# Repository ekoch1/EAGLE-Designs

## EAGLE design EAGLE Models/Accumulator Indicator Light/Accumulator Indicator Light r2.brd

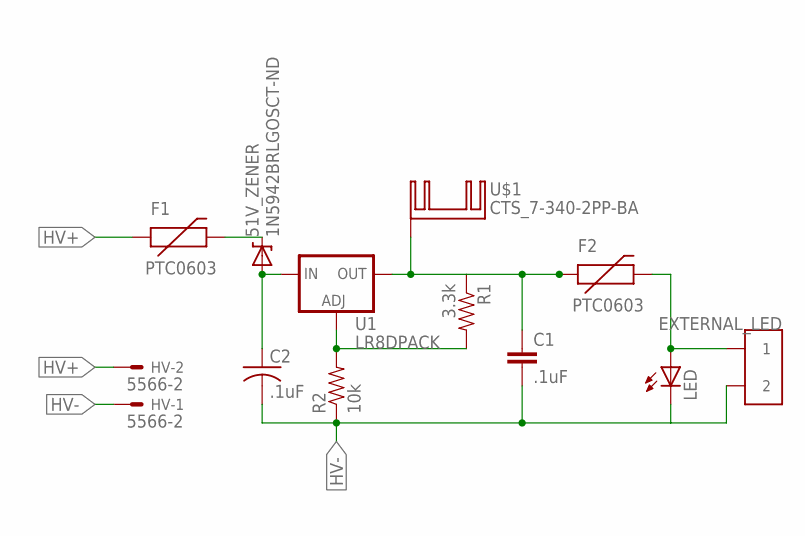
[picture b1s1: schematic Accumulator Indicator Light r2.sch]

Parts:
51V_ZENER: 1N5942BRLGOSCT-ND; DIODE-ZENER
C1: .1uF; 0603-CAP
C2: .1uF; C2220
EXTERNAL_LED: CONN_2; CONNECTOR_2
F1, F2: PTC0603; 0603
HV: 5566-2
LED: LEDSMT1206; 1206
R1: 3.3k; 0603-RES
R2: 10k; 0603-RES
U1: LR8DPACK; DPACK
U$1: CTS_7-340-2PP-BA; TO-200_DUAL

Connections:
HV+: F1.1, HV.2
HV-: C1.2, C2.2, EXTERNAL_LED.3 (2), EXTERNAL_LED.4 (2), HV.1, LED.C, R2.1
N$: 51V_ZENER.P$2 (A), C2.1, U1.1 (IN)
unnamed: R1.2, R2.2, U1.3 (ADJ)
unnamed: C1.1, F2.1, R1.1, U1.4 (OUT), U$1.P$1, U$1.P$2, U$1.P$3
unnamed: 51V_ZENER.P$1 (C), F1.2
unnamed: EXTERNAL_LED.1, EXTERNAL_LED.2 (1), F2.2, LED.A

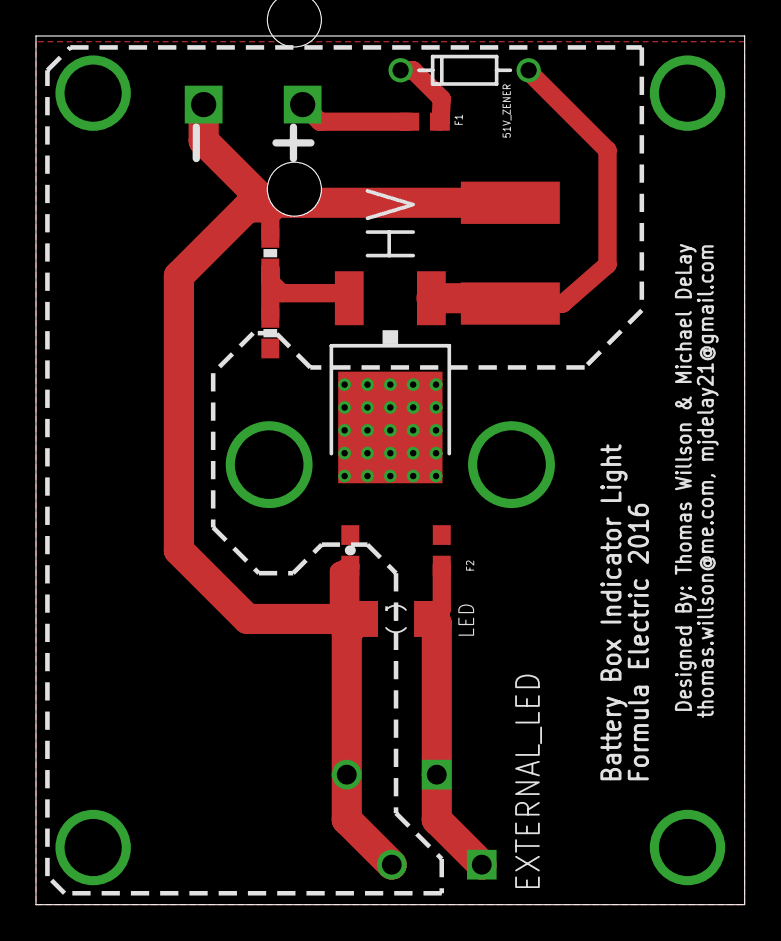
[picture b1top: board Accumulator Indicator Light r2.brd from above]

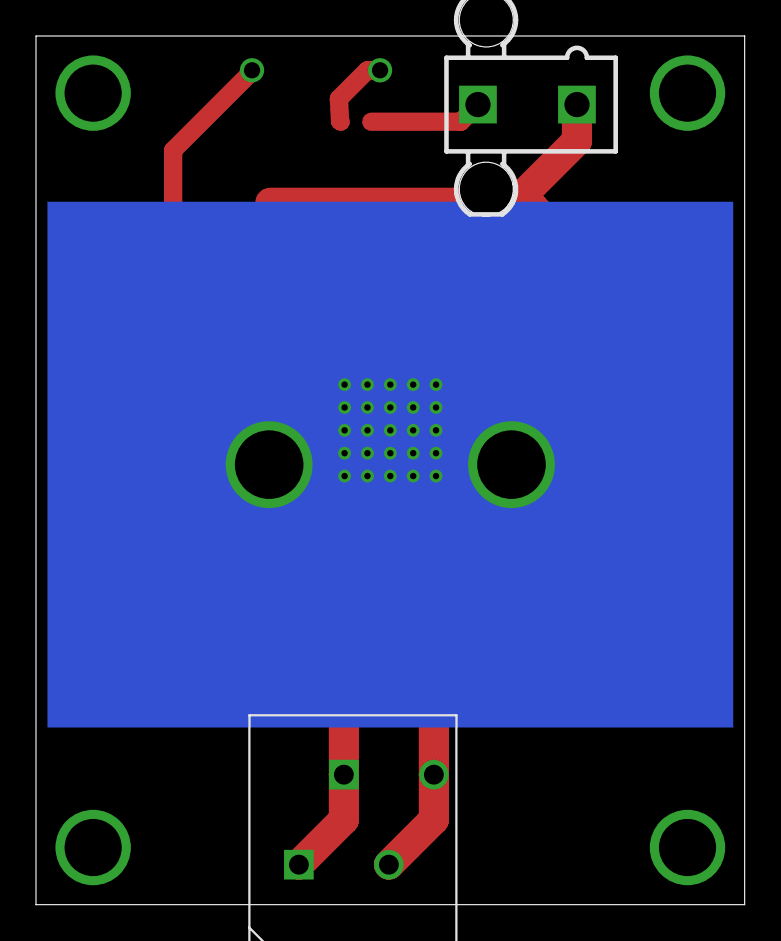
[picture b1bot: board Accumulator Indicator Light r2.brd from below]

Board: 2 copper layers, 39.4 x 48.3 mm, 12 parts (3 on the bottom side), 7 nets.

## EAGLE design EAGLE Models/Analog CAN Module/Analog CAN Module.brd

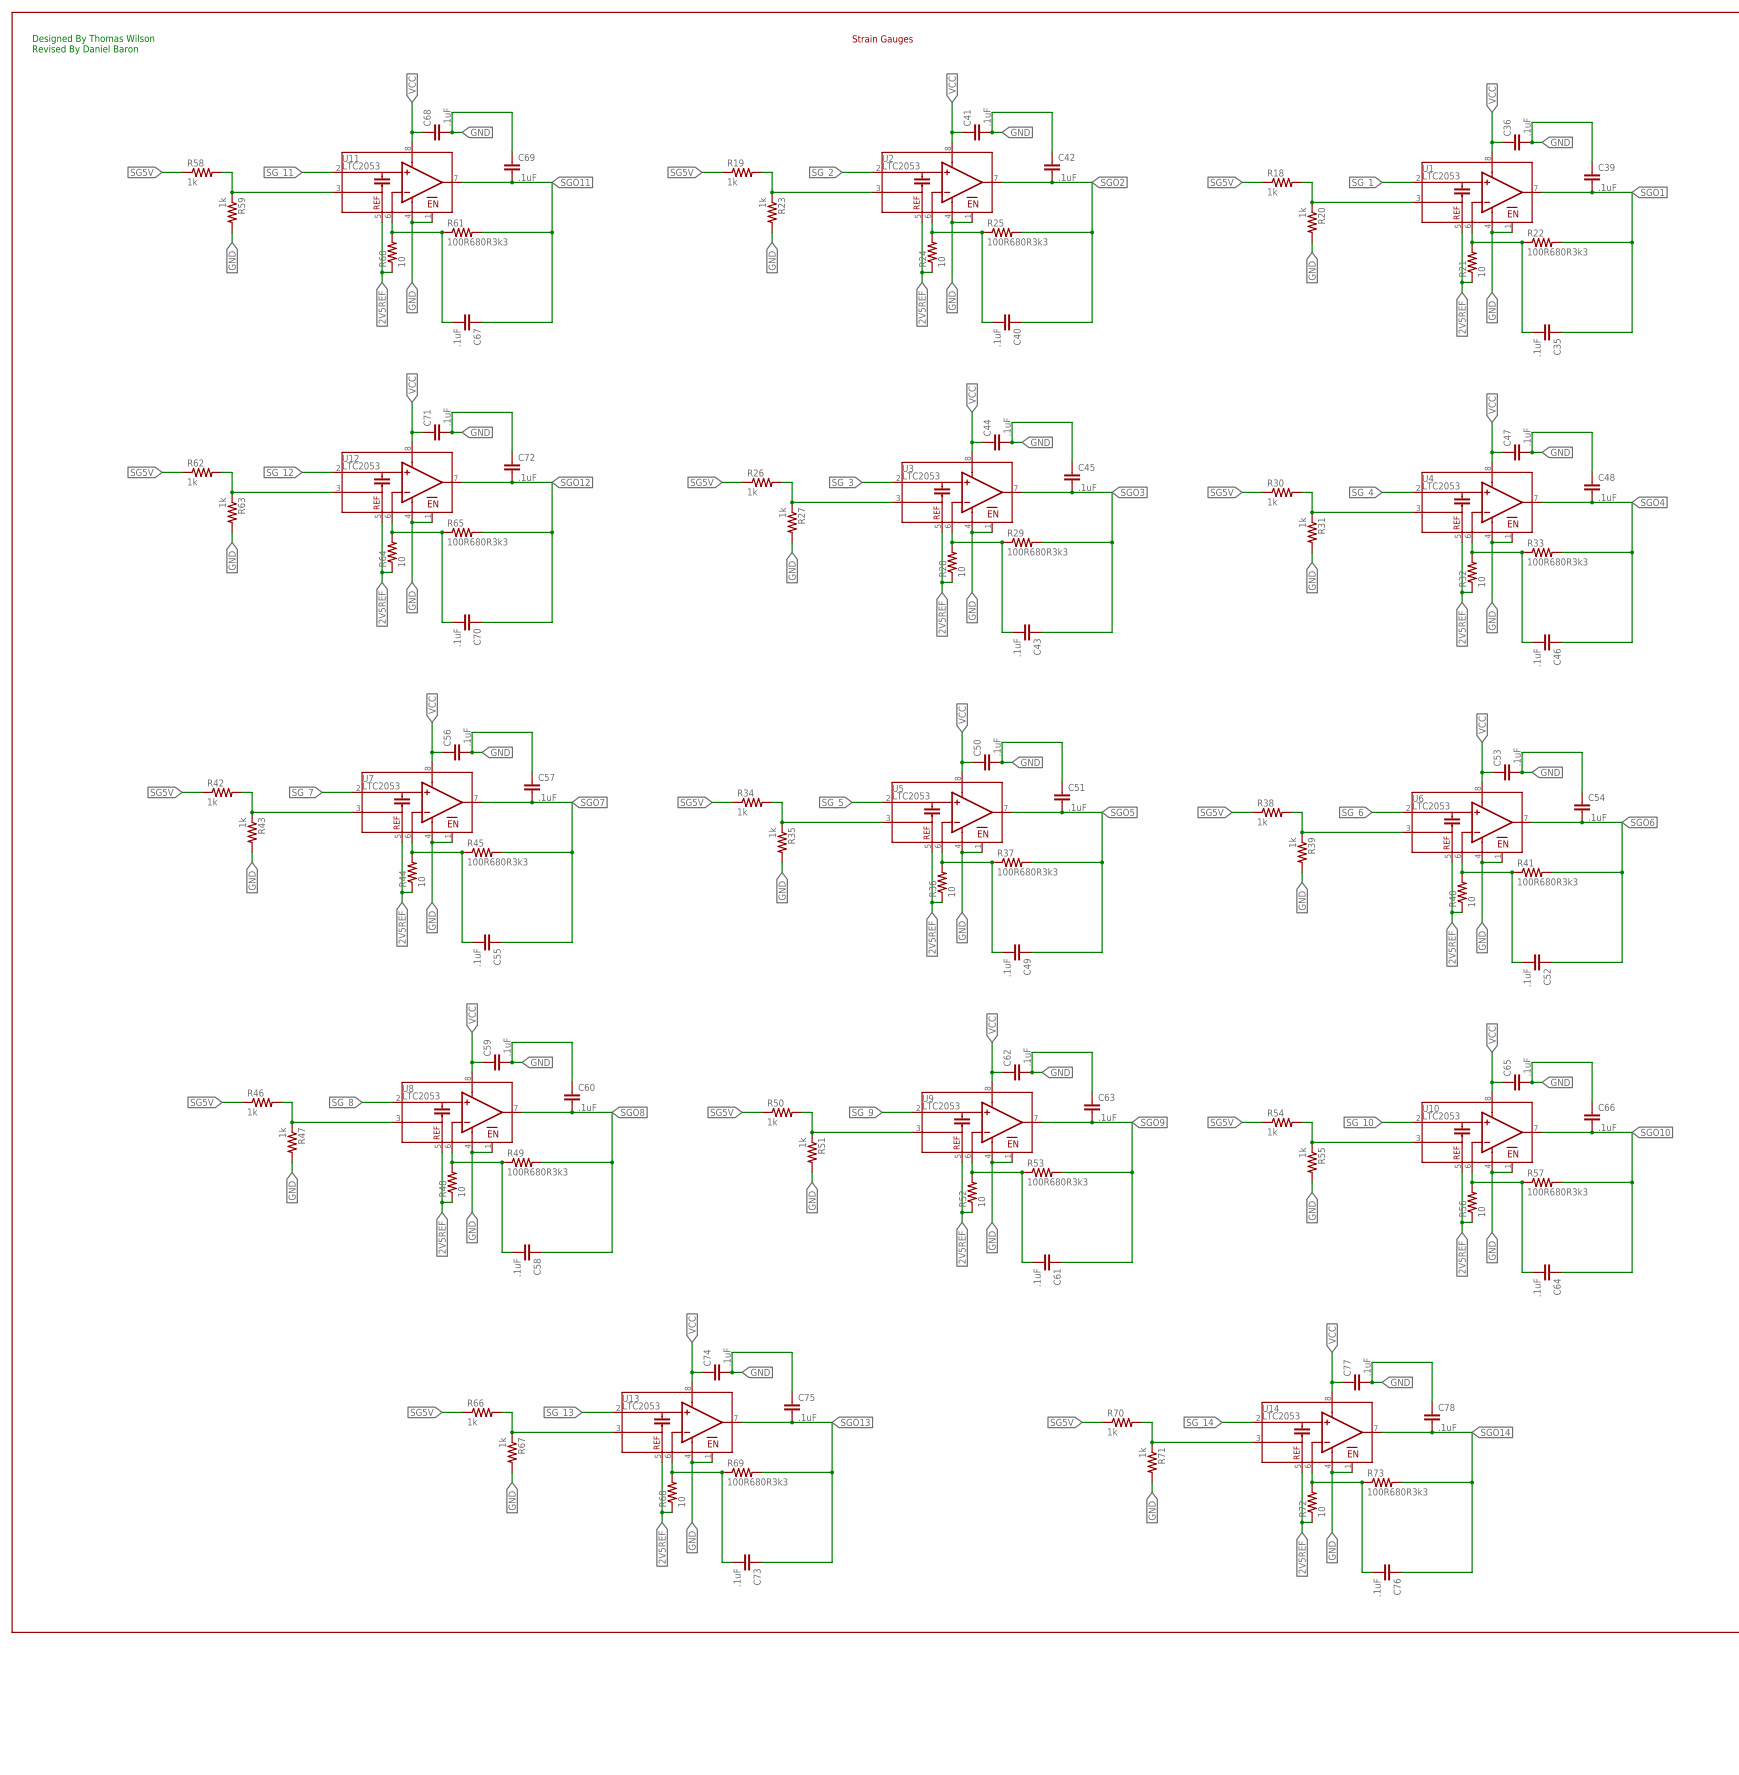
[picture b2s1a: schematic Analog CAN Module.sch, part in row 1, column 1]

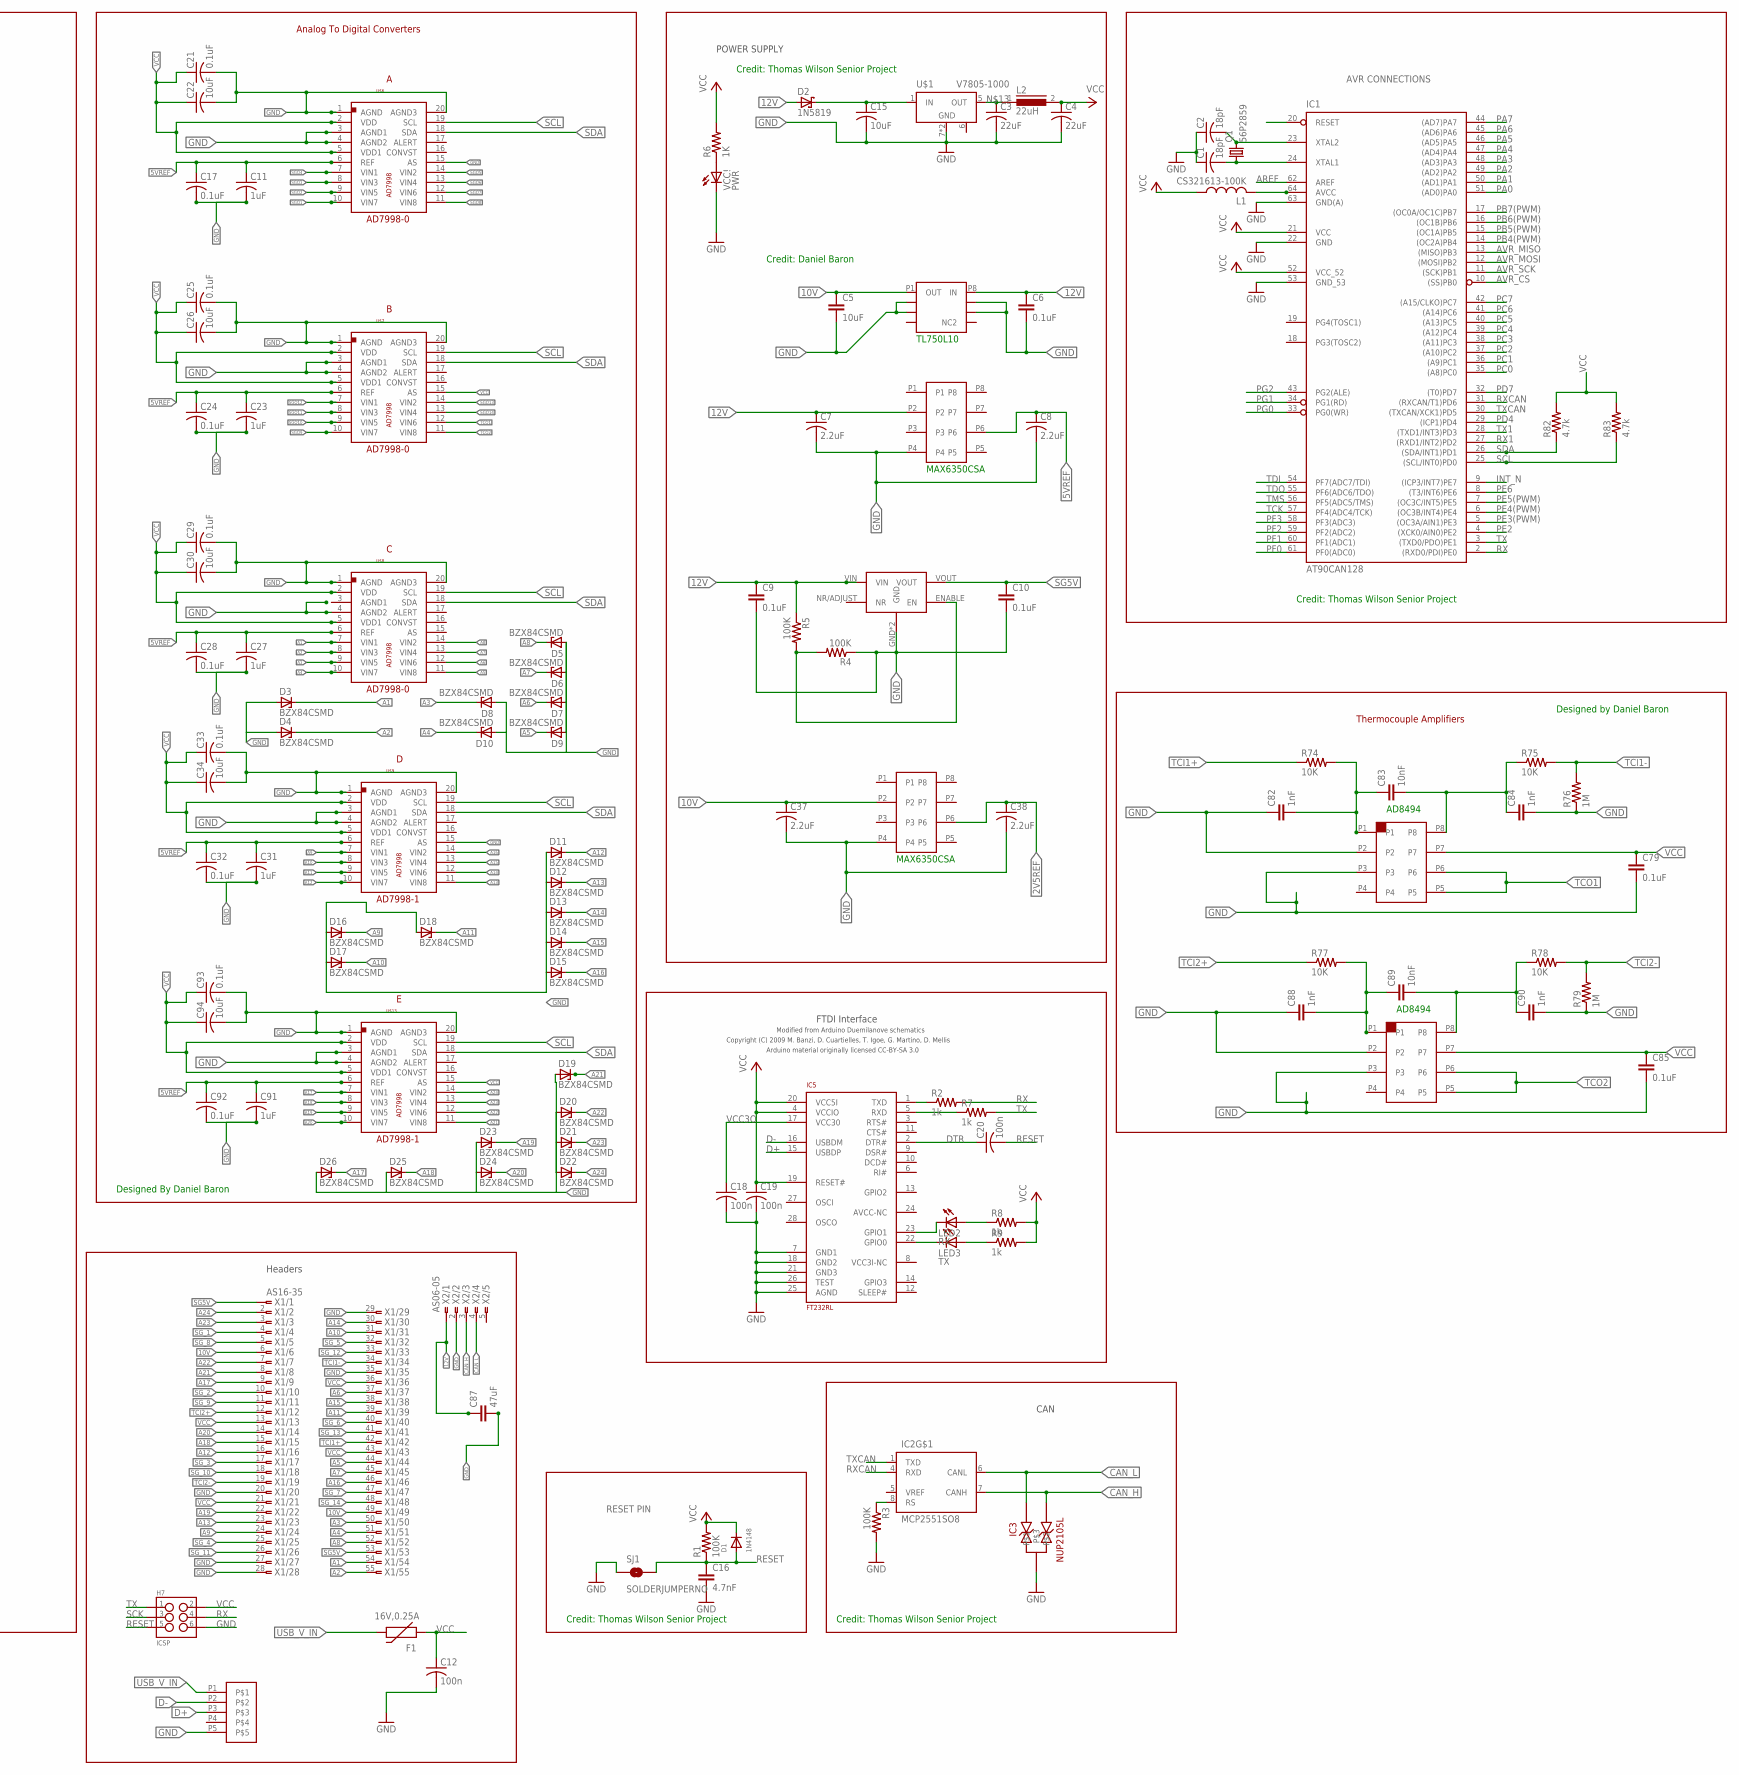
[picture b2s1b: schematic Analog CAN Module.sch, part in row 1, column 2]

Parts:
C1, C2: 18pF; C0805
C3, C4: 22uF; C0805
C5, C15, C22, C26, C30, C34, C94: 10uF; C0805
C6, C9, C10, C17, C21, C24, C25, C28, C29, C32, C33, C79, C85, C92, C93: 0.1uF; C0603
C7, C8, C37, C38: 2.2uF; C0603
C11, C23, C27, C31, C91: 1uF; C0603
C12, C18, C19, C20: 100n; C0805
C16: 4.7nF; 0603-CAP
C35, C36, C39, C40, C41, C42, C43, C44, C45, C46, C47, C48, C49, C50, C51, C52, C53, C54, C55, C56, C57, C58, C59, C60, C61, C62, C63, C64, C65, C66, C67, C68, C69, C70, C71, C72, C73, C74, C75, C76, C77, C78: .1uF; 0603-CAP
C82, C84, C88, C90: 1nF; C0603
C83, C89: 10nF; C0603
C87: 47uF; C0805
D1: 1N4148; SOD-123
D2: 1N5819; DO41-7.6
D3, D4, D5, D6, D7, D8, D9, D10, D11, D12, D13, D14, D15, D16, D17, D18, D19, D20, D21, D22, D23, D24, D25, D26: BZX84CSMD; TO236
F1: 16V,0.25A; PTC-1206
H7: ICSP; 2X3_SMD_FCI_54202-G30
IC1: AT90CAN128; TQFP64
IC2: MCP2551SO8; SO08
IC3: NUP2105L; SOT-23
IC5: FT232RL; SSOP28
L1: CS321613-100K; L3216C
L2: 22uH; DR73
LED2: RX; CHIPLED_0805
LED3: TX; CHIPLED_0805
Q1: 56P2859; HC49UP
R1, R3: 100K; R0805
R2, R7, R8, R9: 1k; R0805
R4, R5: 100K; M0805
R6: 1K; R0805
R18, R19, R20, R23, R26, R27, R30, R31, R34, R35, R38, R39, R42, R43, R46, R47, R50, R51, R54, R55, R58, R59, R62, R63, R66, R67, R70, R71: 1k; 0603-RES
R21, R24, R28, R32, R36, R40, R44, R48, R52, R56, R60, R64, R68, R72: 10; 0603-RES
R22, R25, R29, R33, R37, R41, R45, R49, R53, R57, R61, R65, R69, R73: 100R680R3k3; 0603-RES
R74, R75, R77, R78: 10K; 0603-RES
R76, R79: 1M; 0603-RES
R82, R83: 4.7k; R0805
SJ1: SOLDERJUMPERNO; SJ_2S-NO
U1, U2, U3, U4, U5, U6, U7, U8, U9, U10, U11, U12, U13, U14: LTC2053; MSOP8
U$1: V7805-1000; V78XX-1000
U$2: TL750L10; 8-SOIC
U$4V5V, U$10V2V5: MAX6350CSA; 8-SOIC
U$5: REG-104GA-5; REG104GA-5
U$6, U$7, U$8, U$9, U$13: AD7998; 20TSSOP
U$11, U$12: AD8495; 8MSOP
U$14: MUSBB
VCC!: PWR; CHIPLED_0805
X1: AS16-35
X2: AS06-05

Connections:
2V5REF: C38.1, R21.1, R24.1, R28.1, R32.1, R36.1, R40.1, R44.1, R48.1, R52.1, R56.1, R60.1, R64.1, R68.1, R72.1, U1.5 (REF), U2.5 (REF), U3.5 (REF), U4.5 (REF), U5.5 (REF), U6.5 (REF), U7.5 (REF), U8.5 (REF), U9.5 (REF), U10.5 (REF), U11.5 (REF), U12.5 (REF), U13.5 (REF), U14.5 (REF), U$10V2V5.P6
5VREF: C8.1, C11.1, C17.1, C23.1, C24.1, C27.1, C28.1, C31.1, C32.1, C91.1, C92.1, U$4V5V.P6, U$6.6 (REF), U$7.6 (REF), U$8.6 (REF), U$9.6 (REF), U$13.6 (REF)
10V: C5.1, C37.1, U$2.P1 (OUT), U$10V2V5.P2, X1.6, X1.49
12V: C6.1, C7.1, C9.1, C87.1, D2.A, R5.1, U$2.P8 (IN), U$4V5V.P2, U$5.VIN, X2.1
12V_PROTECTED: C15.1, D2.C, U$1.1 (IN)
A1: D3.C, U$8.7 (VIN1), X1.54
A2: D4.C, U$8.8 (VIN3), X1.55
A3: D8.C, U$8.9 (VIN5), X1.50
A4: D10.C, U$8.10 (VIN7), X1.51
A5: D9.C, U$8.11 (VIN8), X1.44
A6: D7.C, U$8.12 (VIN6), X1.37
A7: D6.C, U$8.13 (VIN4), X1.45
A8: D5.C, U$8.14 (VIN2), X1.52
A9: D16.C, U$9.7 (VIN1), X1.24
A10: D17.C, U$9.8 (VIN3), X1.31
A11: D18.C, U$9.9 (VIN5), X1.39
A12: D11.C, U$9.10 (VIN7), X1.16
A13: D12.C, U$9.11 (VIN8), X1.23
A14: D13.C, U$9.12 (VIN6), X1.30
A15: D14.C, U$9.13 (VIN4), X1.38
A16: D15.C, U$9.14 (VIN2), X1.46
A17: D26.C, U$13.7 (VIN1), X1.9
A18: D25.C, U$13.8 (VIN3), X1.15
A19: D23.C, U$13.9 (VIN5), X1.22
A20: D24.C, U$13.10 (VIN7), X1.14
A21: D19.C, U$13.11 (VIN8), X1.8
A22: D20.C, U$13.12 (VIN6), X1.7
A23: D21.C, U$13.13 (VIN4), X1.3
A24: D22.C, U$13.14 (VIN2), X1.2
AREF: IC1.62 (AREF)
AVR_CS: IC1.10 ((SS)PB0)
AVR_MISO: IC1.13 ((MISO)PB3)
AVR_MOSI: IC1.12 ((MOSI)PB2)
AVR_SCK: IC1.11 ((SCK)PB1)
CAN_H: IC2.7 (CANH), IC3.2, X2.3
CAN_L: IC2.6 (CANL), IC3.1, X2.4
D+: IC5.15 (USBDP), U$14.P3
D-: IC5.16 (USBDM), U$14.P2
DTR: C20.1, IC5.2 (DTR#)
GND: C1.1, C2.1, C3.2, C4.2, C5.2, C6.2, C7.2, C8.2, C9.2, C10.2, C11.2, C12.2, C15.2, C16.2, C17.2, C18.2, C19.2, C21.2, C22.2, C23.2, C24.2, C25.2, C26.2, C27.2, C28.2, C29.2, C30.2, C31.2, C32.2, C33.2, C34.2, C36.2, C37.2, C38.2, C39.1, C41.2, C42.1, C44.2, C45.1, C47.2, C48.1, C50.2, C51.1, C53.2, C54.1, C56.2, C57.1, C59.2, C60.1, C62.2, C63.1, C65.2, C66.1, C68.2, C69.1, C71.2, C72.1, C74.2, C75.1, C77.2, C78.1, C79.2, C82.1, C84.2, C85.2, C87.2, C88.1, C90.2, C91.2, C92.2, C93.2, C94.2, D3.A, D4.A, D5.A, D6.A, D7.A, D8.A, D9.A, D10.A, D11.A, D12.A, D13.A, D14.A, D15.A, D16.A, D17.A, D18.A, D19.A, D20.A, D21.A, D22.A, D23.A, D24.A, D25.A, D26.A, H7.6, IC1.22 (GND), IC1.53 (GND_53), IC1.63 (GND(A)), IC2.2 (GND), IC3.3, IC5.7 (GND1), IC5.18 (GND2), IC5.21 (GND3), IC5.25 (AGND), IC5.26 (TEST), R3.2, R4.1, R20.2, R23.2, R27.2, R31.2, R35.2, R39.2, R43.2, R47.2, R51.2, R55.2, R59.2, R63.2, R67.2, R71.2, R76.1, R79.1, SJ1.1, U1.1 (EN), U1.4 (V-), U2.1 (EN), U2.4 (V-), U3.1 (EN), U3.4 (V-), U4.1 (EN), U4.4 (V-), U5.1 (EN), U5.4 (V-), U6.1 (EN), U6.4 (V-), U7.1 (EN), U7.4 (V-), U8.1 (EN), U8.4 (V-), U9.1 (EN), U9.4 (V-), U10.1 (EN), U10.4 (V-), U11.1 (EN), U11.4 (V-), U12.1 (EN), U12.4 (V-), U13.1 (EN), U13.4 (V-), U14.1 (EN), U14.4 (V-), U$1.7 (GND), U$1.9 (GND), U$2.P2 (COM), U$2.P3 (COM2), U$2.P6 (COM3), U$2.P7 (COM4), U$4V5V.P4, U$5.GND, U$5.HEATGND (GND), U$6.1 (AGND), U$6.3 (AGND1), U$6.4 (AGND2), U$6.15 (AS), U$6.20 (AGND3), U$7.1 (AGND), U$7.3 (AGND1), U$7.4 (AGND2), U$7.20 (AGND3), U$8.1 (AGND), U$8.4 (AGND2), U$8.20 (AGND3), U$9.1 (AGND), U$9.3 (AGND1), U$9.4 (AGND2), U$9.15 (AS), U$9.20 (AGND3), U$10V2V5.P4, U$11.P2, U$11.P3, U$12.P2, U$12.P3, U$13.1 (AGND), U$13.3 (AGND1), U$13.4 (AGND2), U$13.20 (AGND3), U$14.P5, VCC!.C, X1.20, X1.27, X1.28, X1.29, X1.35, X2.2
INT_N: IC1.9 ((ICP3/INT7)PE7)
M8RXD: IC5.1 (TXD), R2.1
M8TXD: IC5.5 (RXD), R7.1
unnamed: C35.2, R21.2, R22.1, U1.6 (RG)
unnamed: R4.2, R5.2, U$5.ENABLE (EN)
unnamed: R66.2, R67.1, U13.3 (+IN)
unnamed: R18.2, R20.1, U1.3 (+IN)
unnamed: R19.2, R23.1, U2.3 (+IN)
unnamed: IC2.8 (RS), R3.1
unnamed: C40.2, R24.2, R25.1, U2.6 (RG)
unnamed: R26.2, R27.1, U3.3 (+IN)
unnamed: R6.1, VCC!.A
unnamed: C43.2, R28.2, R29.1, U3.6 (RG)
unnamed: C1.2, IC1.24 (XTAL1), Q1.1
unnamed: R30.2, R31.1, U4.3 (+IN)
unnamed: C3.1, L2.1, U$1.5 (OUT)
unnamed: C46.2, R32.2, R33.1, U4.6 (RG)
unnamed: R34.2, R35.1, U5.3 (+IN)
unnamed: C49.2, R36.2, R37.1, U5.6 (RG)
unnamed: R38.2, R39.1, U6.3 (+IN)
unnamed: C52.2, R40.2, R41.1, U6.6 (RG)
unnamed: R42.2, R43.1, U7.3 (+IN)
unnamed: C55.2, R44.2, R45.1, U7.6 (RG)
unnamed: R46.2, R47.1, U8.3 (+IN)
unnamed: IC1.64 (AVCC), L1.2
unnamed: C58.2, R48.2, R49.1, U8.6 (RG)
unnamed: R50.2, R51.1, U9.3 (+IN)
unnamed: C61.2, R52.2, R53.1, U9.6 (RG)
unnamed: R54.2, R55.1, U10.3 (+IN)
unnamed: C64.2, R56.2, R57.1, U10.6 (RG)
unnamed: R58.2, R59.1, U11.3 (+IN)
unnamed: C67.2, R60.2, R61.1, U11.6 (RG)
unnamed: R62.2, R63.1, U12.3 (+IN)
unnamed: C70.2, R64.2, R65.1, U12.6 (RG)
unnamed: IC5.23 (GPIO1), LED2.C
unnamed: C73.2, R68.2, R69.1, U13.6 (RG)
unnamed: IC5.22 (GPIO0), LED3.C
unnamed: LED2.A, R8.1
unnamed: LED3.A, R9.1
unnamed: R70.2, R71.1, U14.3 (+IN)
unnamed: C76.2, R72.2, R73.1, U14.6 (RG)
unnamed: C88.2, C89.1, R77.2, U$12.P1
unnamed: C83.2, C84.1, R75.1, U$11.P8
unnamed: C89.2, C90.1, R78.1, U$12.P8
unnamed: C82.2, C83.1, R74.2, U$11.P1
PA0: IC1.51 ((AD0)PA0)
PA1: IC1.50 ((AD1)PA1)
PA2: IC1.49 ((AD2)PA2)
PA3: IC1.48 ((AD3)PA3)
PA4: IC1.47 ((AD4)PA4)
PA5: IC1.46 ((AD5)PA5)
PA6: IC1.45 ((AD6)PA6)
PA7: IC1.44 ((AD7)PA7)
PB4(PWM): IC1.14 ((OC2A)PB4)
PB5(PWM): IC1.15 ((OC1A)PB5)
PB6(PWM): IC1.16 ((OC1B)PB6)
PB7(PWM): IC1.17 ((OC0A/OC1C)PB7)
PC0: IC1.35 ((A8)PC0)
PC1: IC1.36 ((A9)PC1)
PC2: IC1.37 ((A10)PC2)
PC3: IC1.38 ((A11)PC3)
PC4: IC1.39 ((A12)PC4)
PC5: IC1.40 ((A13)PC5)
PC6: IC1.41 ((A14)PC6)
PC7: IC1.42 ((A15/CLKO)PC7)
PD4: IC1.29 ((ICP1)PD4)
PD7: IC1.32 ((T0)PD7)
PE2: IC1.4 ((XCK0/AIN0)PE2)
PE3(PWM): IC1.5 ((OC3A/AIN1)PE3)
PE4(PWM): IC1.6 ((OC3B/INT4)PE4)
PE5(PWM): IC1.7 ((OC3C/INT5)PE5)
PE6: IC1.8 ((T3/INT6)PE6)
PF0: IC1.61 (PF0(ADC0))
PF1: IC1.60 (PF1(ADC1))
PF2: IC1.59 (PF2(ADC2))
PF3: IC1.58 (PF3(ADC3))
PG0: IC1.33 (PG0(WR))
PG1: IC1.34 (PG1(RD))
PG2: IC1.43 (PG2(ALE))
RESET: C16.1, C20.2, D1.A, H7.5, IC1.20 (RESET), R1.1, SJ1.2
RX: H7.4, IC1.2 ((RXD0/PDI)PE0), R2.2
RX1: IC1.27 ((RXD1/INT2)PD2)
RXCAN: IC1.31 ((RXCAN/T1)PD6), IC2.4 (RXD)
SCK: H7.3
SCL: IC1.25 ((SCL/INT0)PD0), R83.1, U$6.19 (SCL), U$7.19 (SCL), U$8.19 (SCL), U$9.19 (SCL), U$13.19 (SCL)
SDA: IC1.26 ((SDA/INT1)PD1), R82.1, U$6.18 (SDA), U$7.18 (SDA), U$8.18 (SDA), U$9.18 (SDA), U$13.18 (SDA)
SG5V: C10.1, R18.1, R19.1, R26.1, R30.1, R34.1, R38.1, R42.1, R46.1, R50.1, R54.1, R58.1, R62.1, R66.1, R70.1, U$5.VOUT, X1.1, X1.53
SGO1: C35.1, C39.2, R22.2, U1.7 (OUT), U$6.10 (VIN7)
SGO2: C40.1, C42.2, R25.2, U2.7 (OUT), U$6.9 (VIN5)
SGO3: C43.1, C45.2, R29.2, U3.7 (OUT), U$6.8 (VIN3)
SGO4: C46.1, C48.2, R33.2, U4.7 (OUT), U$6.7 (VIN1)
SGO5: C49.1, C51.2, R37.2, U5.7 (OUT), U$6.14 (VIN2)
SGO6: C52.1, C54.2, R41.2, U6.7 (OUT), U$6.13 (VIN4)
SGO7: C55.1, C57.2, R45.2, U7.7 (OUT), U$6.12 (VIN6)
SGO8: C58.1, C60.2, R49.2, U8.7 (OUT), U$6.11 (VIN8)
SGO9: C61.1, C63.2, R53.2, U9.7 (OUT), U$7.10 (VIN7)
SGO10: C64.1, C66.2, R57.2, U10.7 (OUT), U$7.9 (VIN5)
SGO11: C67.1, C69.2, R61.2, U11.7 (OUT), U$7.8 (VIN3)
SGO12: C70.1, C72.2, R65.2, U12.7 (OUT), U$7.7 (VIN1)
SGO13: C73.1, C75.2, R69.2, U13.7 (OUT), U$7.14 (VIN2)
SGO14: C76.1, C78.2, R73.2, U14.7 (OUT), U$7.13 (VIN4)
SG_1: U1.2 (-IN), X1.4
SG_2: U2.2 (-IN), X1.10
SG_3: U3.2 (-IN), X1.17
SG_4: U4.2 (-IN), X1.25
SG_5: U5.2 (-IN), X1.32
SG_6: U6.2 (-IN), X1.40
SG_7: U7.2 (-IN), X1.47
SG_8: U8.2 (-IN), X1.5
SG_9: U9.2 (-IN), X1.11
SG_10: U10.2 (-IN), X1.18
SG_11: U11.2 (-IN), X1.26
SG_12: U12.2 (-IN), X1.33
SG_13: U13.2 (-IN), X1.41
SG_14: U14.2 (-IN), X1.48
TCI1+: R74.1, X1.42
TCI1-: R75.2, R76.2, X1.34
TCI2+: R77.1, X1.12
TCI2-: R78.2, R79.2, X1.19
TCK: IC1.57 (PF4(ADC4/TCK))
TCO1: U$7.12 (VIN6), U$11.P5, U$11.P6
TCO2: U$7.11 (VIN8), U$12.P5, U$12.P6
TDI: IC1.54 (PF7(ADC7/TDI))
TDO: IC1.55 (PF6(ADC6/TDO))
TMS: IC1.56 (PF5(ADC5/TMS))
TX: H7.1, IC1.3 ((TXD0/PDO)PE1), R7.2
TX1: IC1.28 ((TXD1/INT3)PD3)
TXCAN: IC1.30 ((TXCAN/XCK1)PD5), IC2.1 (TXD)
USB_V_IN: F1.2, U$14.P1
VCC: C4.1, C12.1, C19.1, C21.1, C22.1, C25.1, C26.1, C29.1, C30.1, C33.1, C34.1, C36.1, C41.1, C44.1, C47.1, C50.1, C53.1, C56.1, C59.1, C62.1, C65.1, C68.1, C71.1, C74.1, C77.1, C79.1, C85.1, C93.1, C94.1, D1.C, F1.1, H7.2, IC1.21 (VCC), IC1.52 (VCC_52), IC2.3 (VCC), IC5.4 (VCCIO), IC5.19 (RESET#), IC5.20 (VCC5I), L1.1, L2.2, R1.2, R6.2, R8.2, R9.2, R82.2, R83.2, U1.8 (V+), U2.8 (V+), U3.8 (V+), U4.8 (V+), U5.8 (V+), U6.8 (V+), U7.8 (V+), U8.8 (V+), U9.8 (V+), U10.8 (V+), U11.8 (V+), U12.8 (V+), U13.8 (V+), U14.8 (V+), U$6.2 (VDD), U$6.5 (VDD1), U$7.2 (VDD), U$7.5 (VDD1), U$7.15 (AS), U$8.2 (VDD), U$8.5 (VDD1), U$9.2 (VDD), U$9.5 (VDD1), U$11.P7, U$12.P7, U$13.2 (VDD), U$13.5 (VDD1), U$13.15 (AS), X1.13, X1.21, X1.36, X1.43
VCC3O: C18.1, IC5.17 (VCC30)
XTAL1: C2.2, IC1.23 (XTAL2), Q1.2

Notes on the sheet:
POWER SUPPLY
CAN
RESET PIN
AVR CONNECTIONS
FTDI Interface
Headers
Modified from Arduino Duemilanove schematics
Copyright (C) 2009 M. Banzi, D. Cuartielles, T. Igoe, G. Martino, D. Mellis
Arduino material originally licensed CC-BY-SA 3.0
TL750L10
MAX6350CSA
AD7998-0
AD7998-1
Analog To Digital Converters
Strain Gauges
Thermocouple Amplifiers
Credit: Thomas Wilson Senior Project
Designed By Thomas Wilson Revised By Daniel Baron
Designed By Daniel Baron
Designed by Daniel Baron
Credit: Daniel Baron
AD8494

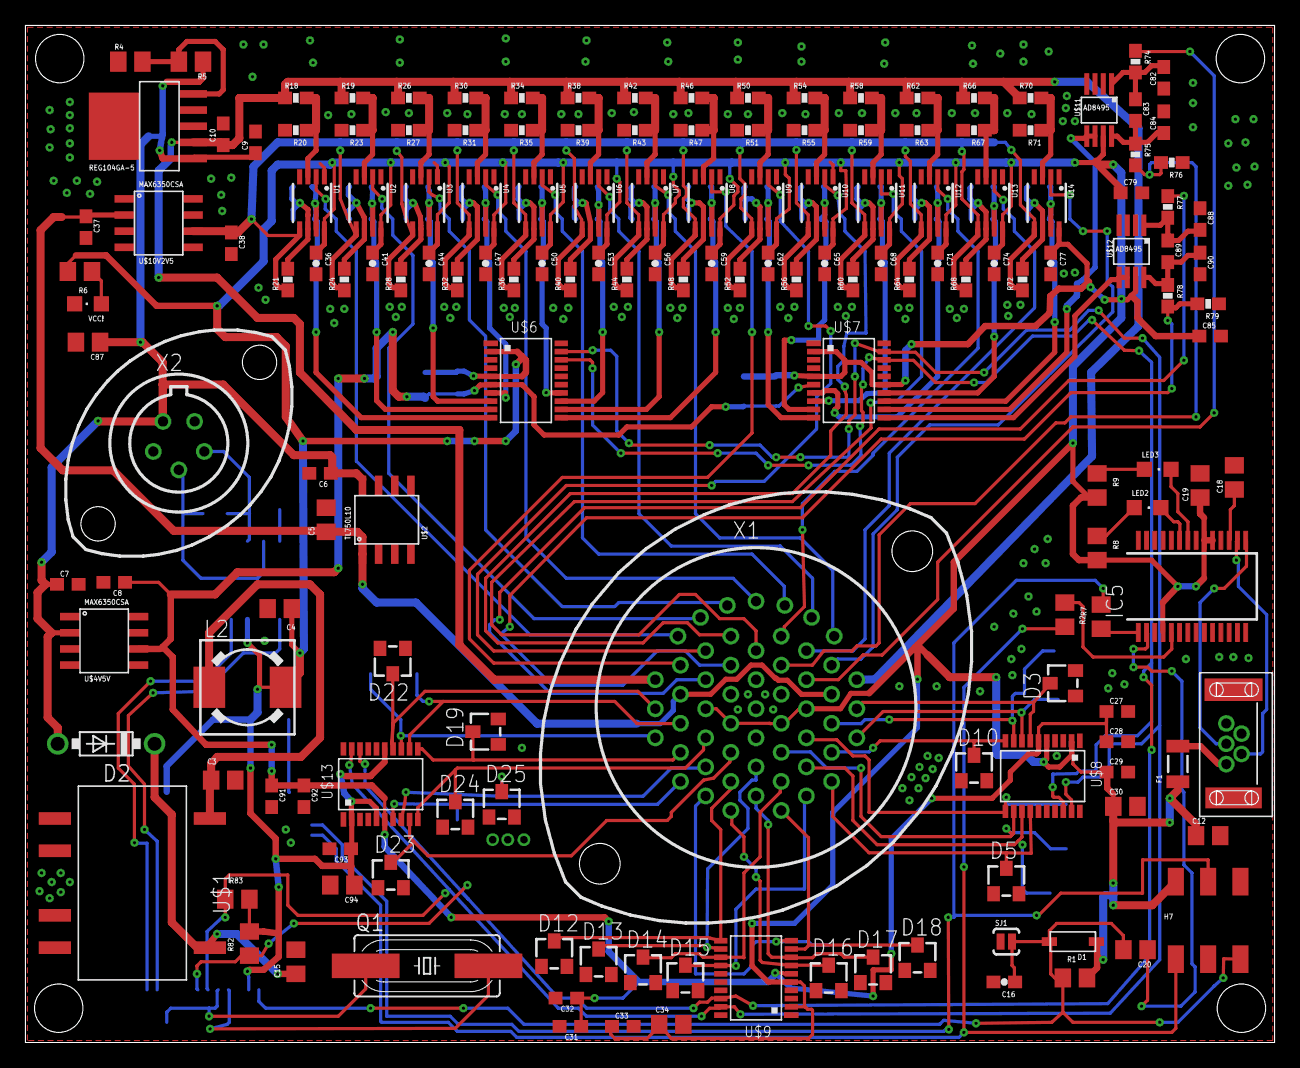
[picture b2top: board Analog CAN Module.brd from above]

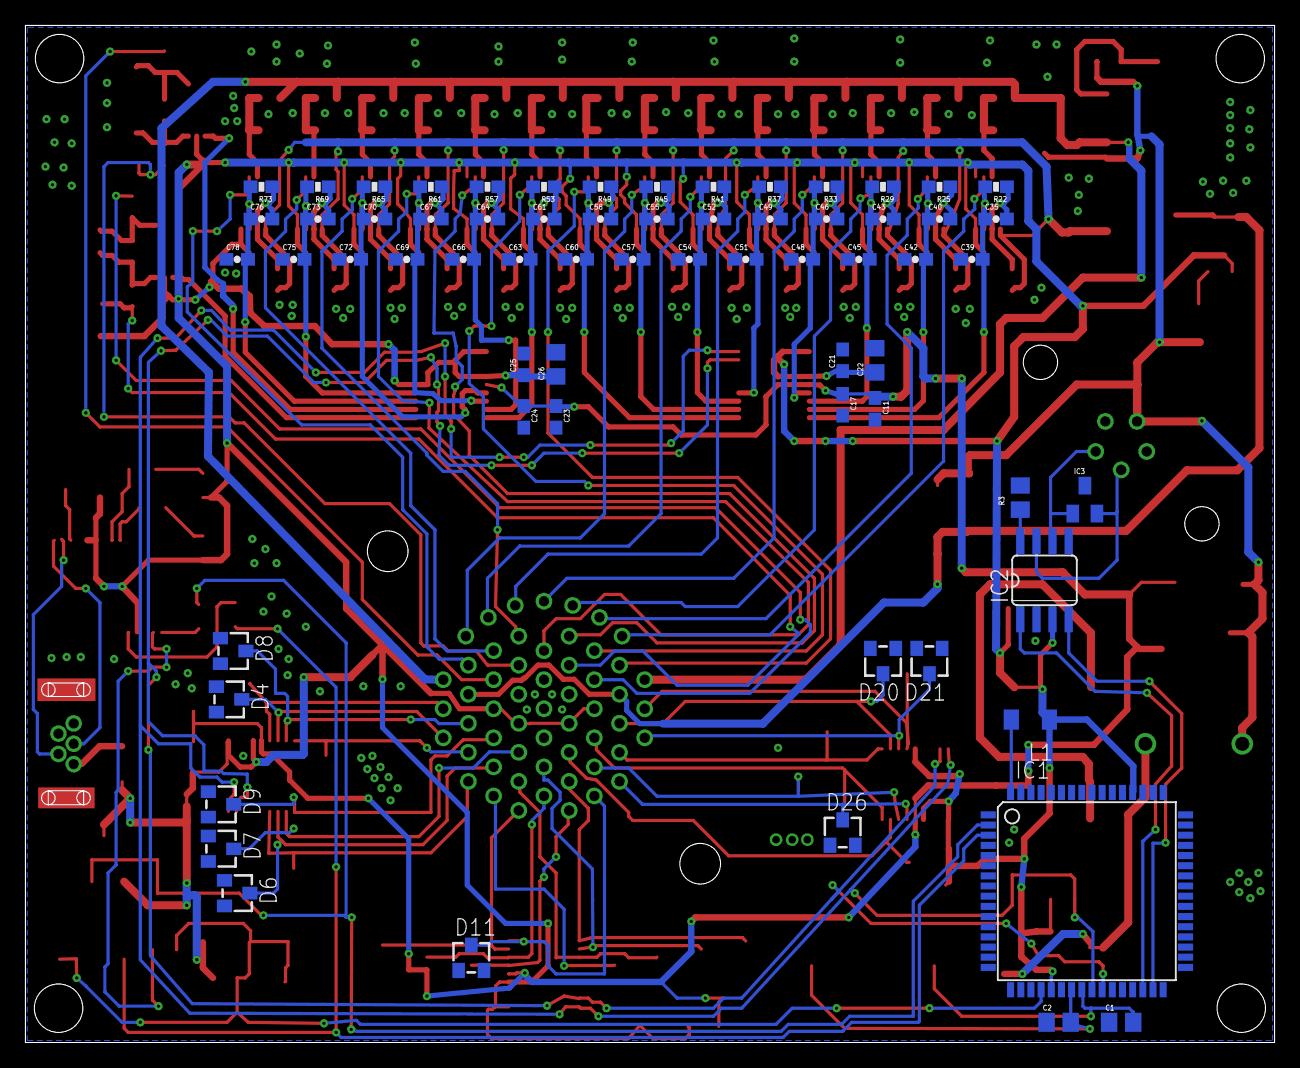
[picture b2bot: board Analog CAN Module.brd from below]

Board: 2 copper layers, 98.3 x 80.0 mm, 230 parts (66 on the bottom side), 125 nets.

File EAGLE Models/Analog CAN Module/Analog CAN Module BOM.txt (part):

Partlist exported from C:/Users/Daniel Baron/Desktop/FSAE2016Boards and Schematics/CAN_MOD_12-12.sch at 1/11/2016 3:44 PM

Part     Value          Device          Package               Description                                                                         MF MPN OC_FARNELL OC_NEWARK
C1       18pF           C-USC0805       C0805                 CAPACITOR, American symbol                                                                                     
C2       18pF           C-USC0805       C0805                 CAPACITOR, American symbol                                                                                     
C3       22uF           C-USC0805       C0805                 CAPACITOR, American symbol                                                                                     
C4       22uF           C-USC0805       C0805                 CAPACITOR, American symbol                                                                                     
C5       10uF           C-EUC0805       C0805                 CAPACITOR, European symbol                                                                                     
C6       0.1uF          C-EUC0603       C0603                 CAPACITOR, European symbol                                                                                     
C7       2.2uF          C-USC0603       C0603                 CAPACITOR, American symbol                                                                                     
C8       2.2uF          C-USC0603       C0603                 CAPACITOR, American symbol                                                                                     
C9       0.1uF          C-EUC0603       C0603                 CAPACITOR, European symbol                                                                                     
C10      0.1uF          C-EUC0603       C0603                 CAPACITOR, European symbol                                                                                     
C11      1uF            C-USC0603       C0603                 CAPACITOR, American symbol                                                                                     
C12      100n           C-USC0805       C0805                 CAPACITOR, American symbol                                                                                     
C15      10uF           C-USC0805       C0805                 CAPACITOR, American symbol                                                                                     
C16      4.7nF          CAP0603-CAP     0603-CAP              Capacitor                                                                                                      
C17      0.1uF          C-USC0603       C0603                 CAPACITOR, American symbol                                                                                     
C18      100n           C-USC0805       C0805                 CAPACITOR, American symbol                                                                                     
C19      100n           C-USC0805       C0805                 CAPACITOR, American symbol                                                                                     
C20      100n           C-USC0805       C0805                 CAPACITOR, American symbol                                                                                     
C21      0.1uF          C-USC0603       C0603                 CAPACITOR, American symbol                                                                                     
C22      10uF           C-USC0805       C0805                 CAPACITOR, American symbol                                                                                     
C23      1uF            C-USC0603       C0603                 CAPACITOR, American symbol                                                                                     
C24      0.1uF          C-USC0603       C0603                 CAPACITOR, American symbol                                                                                     
C25      0.1uF          C-USC0603       C0603                 CAPACITOR, American symbol                                                                                     
C26      10uF           C-USC0805       C0805                 CAPACITOR, American symbol                                                                                     
C27      1uF            C-USC0603       C0603                 CAPACITOR, American symbol                                                                                     
C28      0.1uF          C-USC0603       C0603                 CAPACITOR, American symbol                                                                                     
C29      0.1uF          C-USC0603       C0603                 CAPACITOR, American symbol                                                                                     
C30      10uF           C-USC0805       C0805                 CAPACITOR, American symbol                                                                                     
C31      1uF            C-USC0603       C0603                 CAPACITOR, American symbol                                                                                     
C32      0.1uF          C-USC0603       C0603                 CAPACITOR, American symbol                                                                                     
C33      0.1uF          C-USC0603       C0603                 CAPACITOR, American symbol                                                                                     
C34      10uF           C-USC0805       C0805                 CAPACITOR, American symbol                                                                                     
C35      .1uF           CAP0603-CAP     0603-CAP              Capacitor                                                                                                      
C36      .1uF           CAP0603-CAP     0603-CAP              Capacitor                                                                                                      
C37      2.2uF          C-USC0603       C0603                 CAPACITOR, American symbol                                                                                     
C38      2.2uF          C-USC0603       C0603                 CAPACITOR, American symbol                                                                                     
C39      .1uF           CAP0603-CAP     0603-CAP              Capacitor                                                                                                      
C40      .1uF           CAP0603-CAP     0603-CAP              Capacitor                                                                                                      
C41      .1uF           CAP0603-CAP     0603-CAP              Capacitor                                                                                                      
C42      .1uF           CAP0603-CAP     0603-CAP              Capacitor                                                                                                      
C43      .1uF           CAP0603-CAP     0603-CAP              Capacitor                                                                                                      
C44      .1uF           CAP0603-CAP     0603-CAP              Capacitor                                                                                                      
C45      .1uF           CAP0603-CAP     0603-CAP              Capacitor                                                                                                      
C46      .1uF           CAP0603-CAP     0603-CAP              Capacitor                                                                                                      
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

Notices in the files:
parts and their libraries:
SparkFun-Capacitors: Licensing: CC v3.0 Share-Alike You are welcome to use this library for commercial purposes.
